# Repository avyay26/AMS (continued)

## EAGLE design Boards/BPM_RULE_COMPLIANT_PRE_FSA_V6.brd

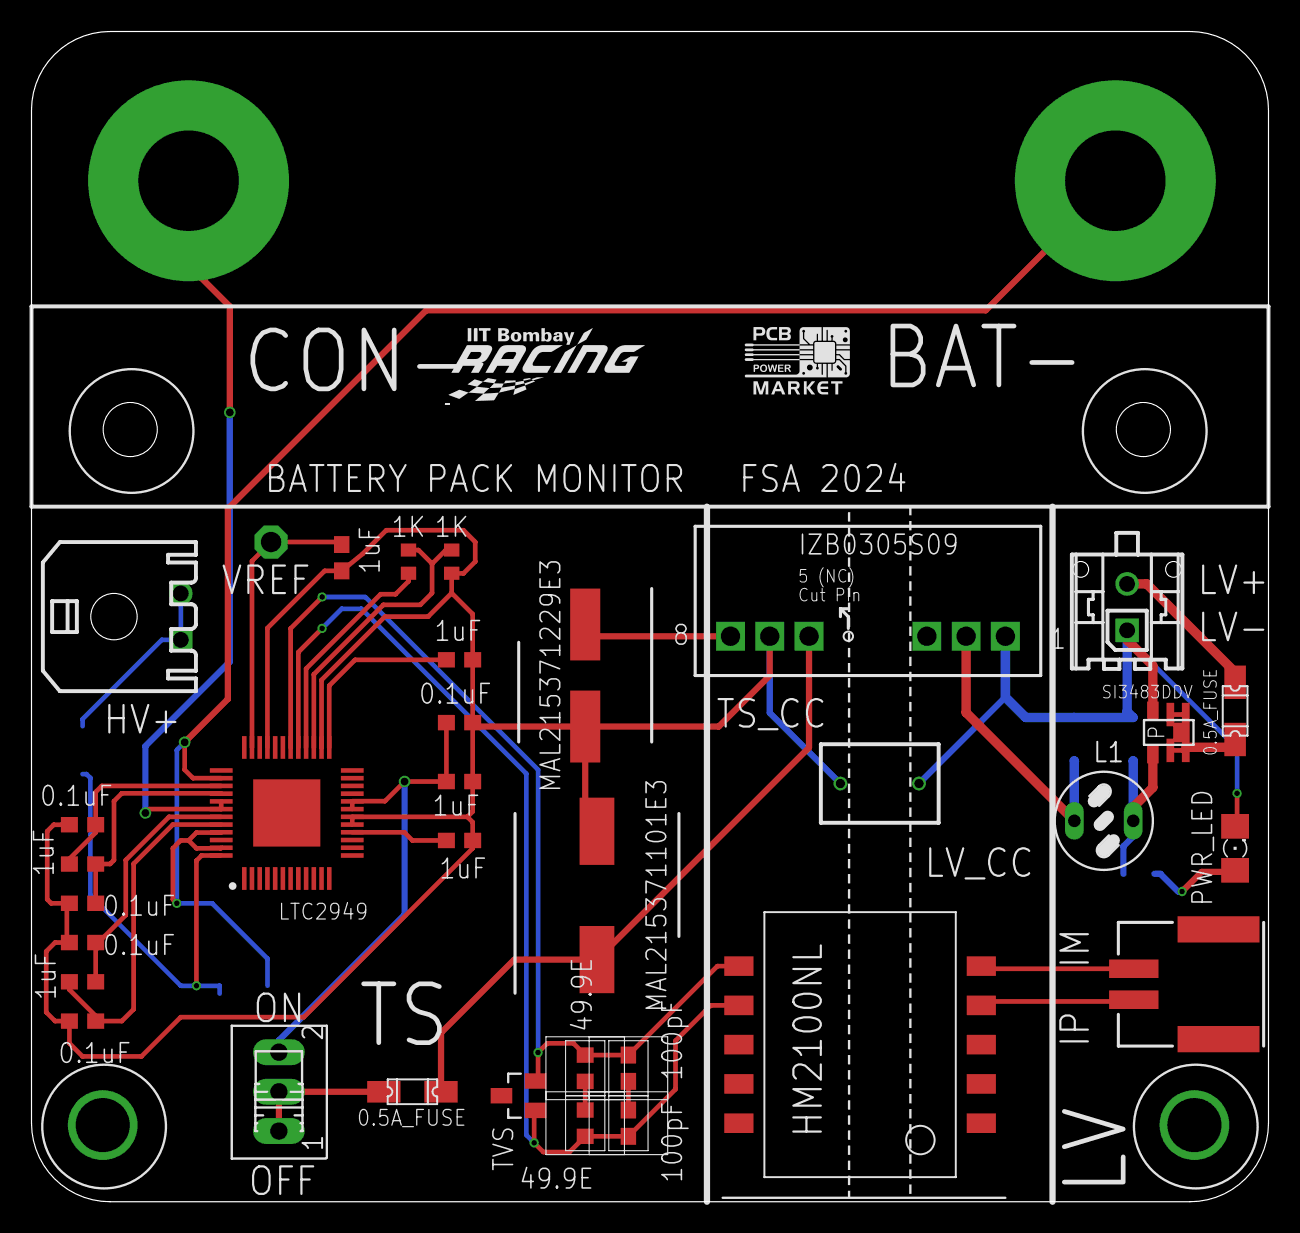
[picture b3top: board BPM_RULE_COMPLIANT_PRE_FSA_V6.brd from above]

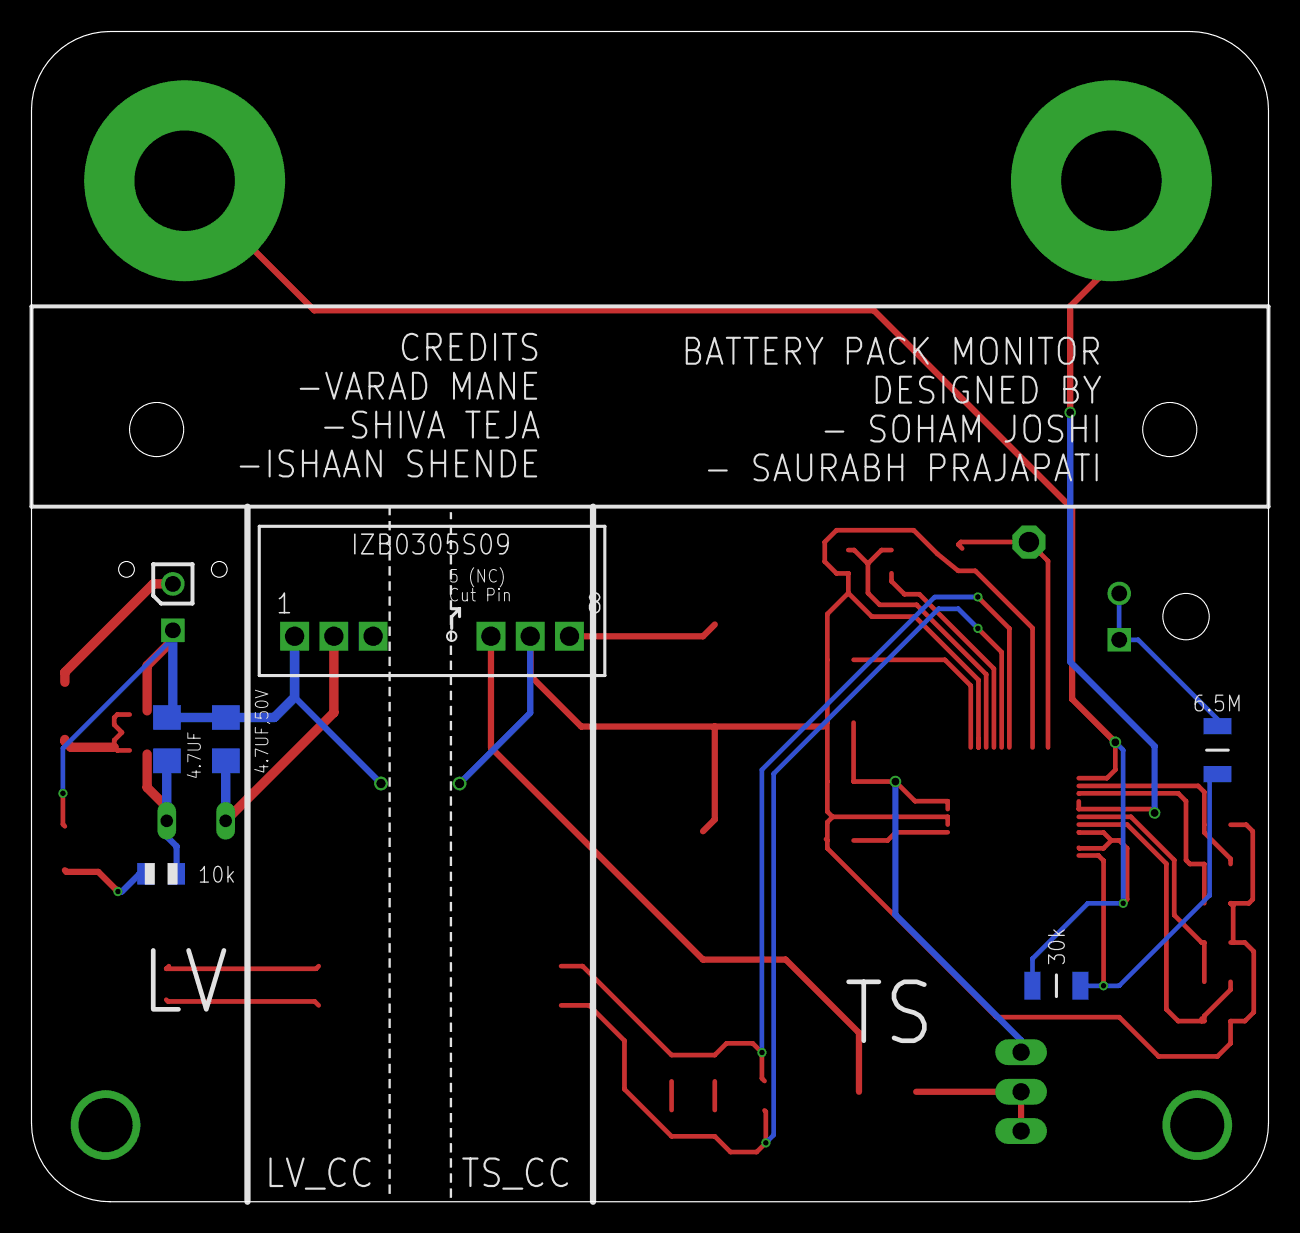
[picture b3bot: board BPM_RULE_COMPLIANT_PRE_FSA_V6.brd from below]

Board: 2 copper layers, 80.0 x 75.7 mm, 41 parts (5 on the bottom side), 30 nets.

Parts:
4.7UF, 4.7UF,50V: C1206
BYP1_FIL, BYP2_FIL: 1uF; C0603
C2: MAL215371101E3; CAPAE1060X1060N
C3: MAL215371229E3; CAPAE860X680N
C15: TPPAD1-13; P1-13
C16, C17: 100pF; C0603
DVCC_FIL: 1uF; C0603
F1, F2: 1206L
HM2100NL: HM2100NL
HV+: 43650-0200
I1G_FIL, I1_G_FIL, I2G_FIL1, I2_G_FIL1: 0.1uF; C0603
I1_FIL, I2_FIL1: 1uF; C0603
IC1: LTC2949HLXE#3ZZPBF; QFP50P900X900X160-49N
IM1: TVS; SOT23
J1: 502352-0200; 5023520200
L1: 82114R
POWER_SUPPLY: 43045-0212
PWR_LED: FKIT-LED-1206
R14: 30k; RESC3216X70N
R15, R16: 1K; RESC1608X50N
R17: 6.5M; RESC3216X70N
R20: 10k; R0805
RM1, RM2: 49.9E; R0603
S1: STS121PC04
S_G_BY: 0.1uF; C0603
U$1: BPM_CONV
U$2: 80-C330C102KGR5TATU
U$6: LOGO_PCBPOWER; 270X170
U$10: TSOP-6_PMOS
U$22: RACING_LOGO_190MIL
VREF_DECOUPLE1: 1uF; C0603

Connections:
12VIN: 4.7UF.1, L1.2, R20.1, U$10.S
12V_ACU_TO_BPM: F2.P$2, U$10.1, U$10.2, U$10.5, U$10.6, U$10.D
+12V: C2.1, F1.P$2, U$1.6
BATP: IC1.48, R14.2, R17.1
BYP1: BYP1_FIL.2, IC1.16
BYP2: BYP2_FIL.1, IC1.25
CF1M: I1G_FIL.1, I1_FIL.1, IC1.43
CF1P: I1_FIL.2, I1_G_FIL.2, IC1.44
CF2M: I2_FIL1.2, I2_G_FIL1.1, IC1.40
CF2P: I2G_FIL1.1, I2_FIL1.1, IC1.39
GND: BYP1_FIL.1, BYP2_FIL.2, C2.2, C3.2, DVCC_FIL.1, I1G_FIL.2, I1_G_FIL.1, I2G_FIL1.2, I2_G_FIL1.2, IC1.17, IC1.18, IC1.26, IC1.33, R16.2, S_G_BY.1, U$1.7, U$2.P$1, VREF_DECOUPLE1.1
GNDIN: 4.7UF.2, 4.7UF,50V.2, POWER_SUPPLY.P$1, PWR_LED.C, U$1.1, U$2.P$2, U$10.G
HV+: HV+.P$1, HV+.P$2, R17.2
HV-: IC1.38, IC1.45, IC1.47, R14.1
I1M: IC1.41, IC1.42
IBIAS: IC1.28, R15.1
ICMP: IC1.27, R15.2, R16.1
ISOA_M: C17.2, HM2100NL.6, IC1.30, IM1.2, RM2.1
ISOA_P: C16.1, HM2100NL.7, IC1.29, IM1.1, RM1.2
ISOB_M: HM2100NL.5, J1.2
ISOB_P: HM2100NL.4, J1.1
N$: RM1.1, RM2.2
unnamed: 4.7UF,50V.1, L1.1, U$1.2
unnamed: F2.P$1, POWER_SUPPLY.P$2
unnamed: PWR_LED.A, R20.2
unnamed: F1.P$1, S1.1, S1.2
unnamed: C16.2, C17.1
RIPPLE: C3.1, U$1.8
VCC: DVCC_FIL.2, IC1.19, IC1.20, S1.3, S_G_BY.2
VREF: C15.TP, IC1.35, VREF_DECOUPLE1.2

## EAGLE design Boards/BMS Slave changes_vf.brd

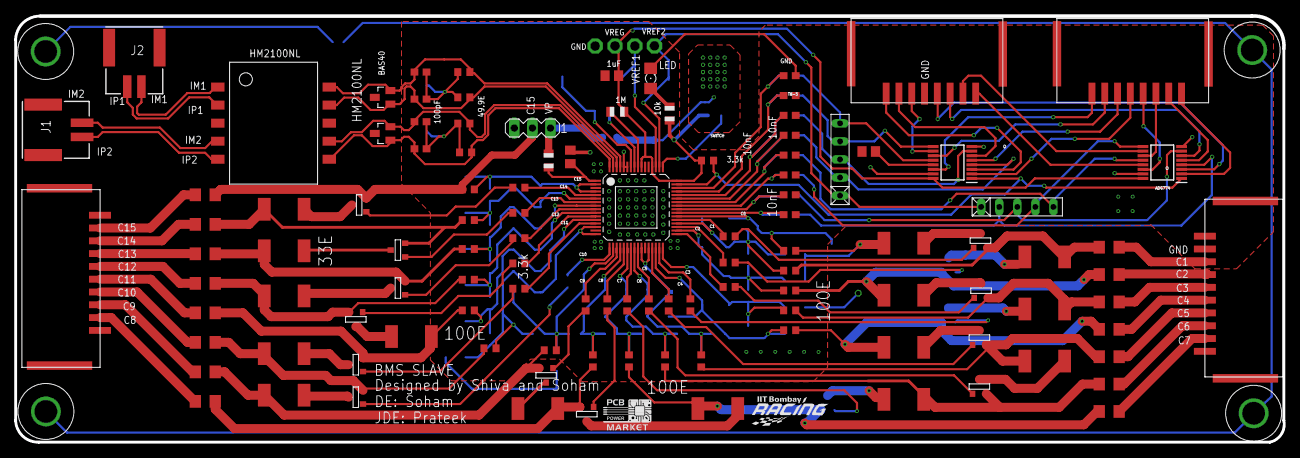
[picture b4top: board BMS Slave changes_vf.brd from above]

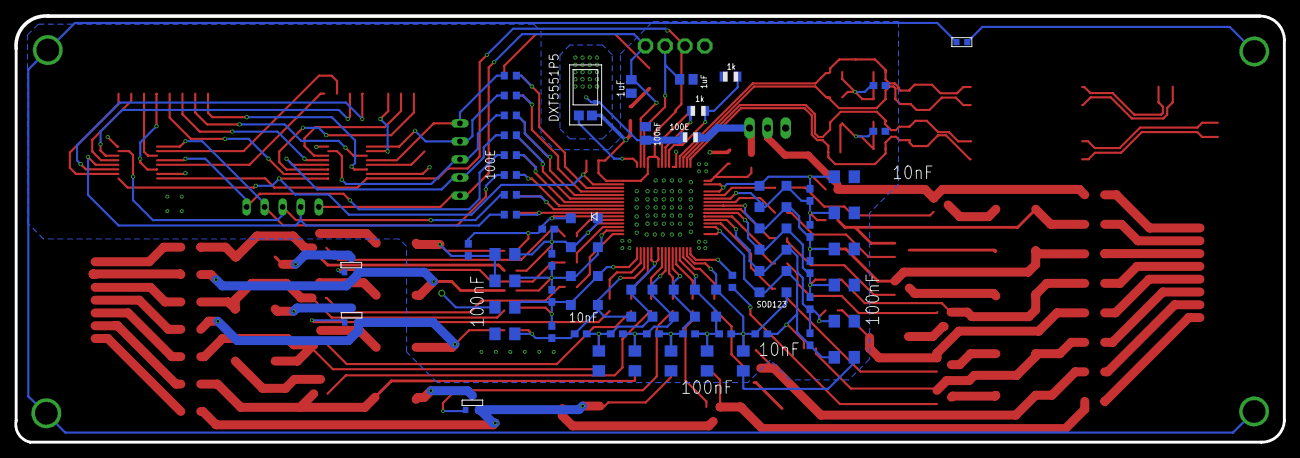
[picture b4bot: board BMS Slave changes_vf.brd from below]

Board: 2 copper layers, 178.5 x 60.0 mm, 185 parts (68 on the bottom side), 146 nets.

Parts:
C1, C175, C177: 1uF; C0805
C2, C3, C5, C6: 100pF; C0603
C4, C8: 10nF; C0603
C173, C176: 100nF; C0805
D1, D2, D3, D4, D5, D7, D8, D9, D10, D11, D12, D13, D14, D15, D16: SOD123
DEMUX1, DEMUX2: ADG774ABRQZ; SOP64P600X175-16N
E0, E1, E2, E3, E4, E5, E7, E8, E9, E10, E11, E12, E13, E14, E15, E16, E18, E19, E20, E21, E22, E23, E24, E25: 100E; R0603
F1, F2, F3, F4, F5, F7, F8, F9, F10, F11, F12, F13, F14, F15, F16: 100nF; C1206
IM1, IM2: BAS40-05; SOT23
J1, J2: 502352-0200; 5023520200
K1, K2, K3, K4, K5, K7, K8, K9, K10, K11, K12, K13, K14, K15, K16, K17: 3.3K; R0603
LED1: 1206
M1, M2, M3, M4, M5, M7, M8, M9, M10, M11, M12, M13, M14, M15, M16: SOT-23
P0, P1, P2, P3, P4, P6, P7, P8, P9, P10, P11, P12, P13, P14, P15: 33E; R2512
R1: 5k; R0805
R2: OE; R0603
R3: 100K; R0805
R157, R161: 100E; R0805
R159, R160: 1k; R0805
R162: 1M; R0805
RM1, RM2, RM3, RM4: 49.9E; R0603
RN2, RN3: 10k; RN-5
SV1: MA03-1
T0, T1, T2, T3, T4, T5, T7, T8, T9, T10, T11, T12, T13, T14, T15, T16, T18, T19, T20, T21, T22, T23, T24, T25: 10nF; C0603
TP1, TP6, TP7, TP8: TPPAD1-13; P1-13
U$1: HM2100NL
U$2: DXT5551P5
U$3: LTC6813
U$4: IITBR_LOGO
U$5, U$6: 1X10NANOMQS
U$7: LOGO_PCBPOWER; 270X170
U$8, U$10: NEWBMS
U$9, U$13, U$14, U$15, U$16, U$17, U$18, U$19, U$20, U$21, U$23, U$24, U$25, U$26, U$27: PTC-FUSE; 1206

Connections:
C: C173.1, R157.1, U$2.C
C01: E1.1, M1.2, P1.2, U$27.2
C02: E2.1, M2.2, P2.2, U$26.2
C03: E3.1, M3.2, P3.2, U$25.2
C04: E4.1, M4.2, P4.2, U$24.2
C05: E5.1, M5.2, P6.2, U$23.2
C06: E7.1, M7.2, P7.2, U$21.2
C07: E8.1, M8.2, P8.2, U$20.2
C08: E9.1, M9.2, P9.2, U$19.2
C09: E10.1, M10.2, P10.2, U$18.2
C10: E11.1, M11.2, P11.2, U$17.2
C11: E12.1, M12.2, P12.2, U$16.2
C12: E13.1, M13.2, P13.2, U$15.2
C13: E14.1, M14.2, P14.2, U$14.2
C14: E15.1, M15.2, P15.2, U$13.2
C15: E16.1, M16.2, SV1.2, U$9.2
C_01: U$6.P$3, U$27.1
C_02: U$6.P$4, U$26.1
C_03: U$6.P$5, U$25.1
C_04: U$6.P$6, U$24.1
C_05: U$6.P$7, U$23.1
C_06: U$6.P$8, U$21.1
C_07: U$6.P$9, U$20.1
C_08: U$5.P$2, U$19.1
C_09: U$5.P$3, U$18.1
C_10: U$5.P$4, U$17.1
C_11: U$5.P$5, U$16.1
C_12: U$5.P$6, U$15.1
C_13: U$5.P$7, U$14.1
C_14: U$5.P$8, U$13.1
C_15: U$5.P$9, U$9.1
C_17: D16.C, E16.2, F16.1, T16.1, U$3.C17, U$3.C18
C_18: D15.C, D16.A, E15.2, F15.1, T15.1, T16.2, U$3.C16
C_20: D14.C, D15.A, E14.2, F14.1, T14.1, T15.2, U$3.C15
C_21: K10.1, M10.3
C_22: D13.C, D14.A, E13.2, F13.1, T13.1, T14.2, U$3.C14
C_23: D9.C, D10.A, E9.2, F9.1, T9.1, T10.2, U$3.C9
C_24: D12.C, D13.A, E12.2, F12.1, T12.1, T13.2, U$3.C13
C_26: D8.C, D9.A, E8.2, F8.1, T8.1, T9.2, U$3.C8
C_27: D10.C, D11.A, E10.2, F10.1, T10.1, T11.2, U$3.C10
C_28: D11.C, D12.A, E11.2, F11.1, T11.1, T12.2, U$3.C11, U$3.C12
C_30: D7.C, D8.A, E7.2, F7.1, T7.1, T8.2, U$3.C7
C_33: D5.C, D7.A, E5.2, F5.2, T5.1, T7.2, U$3.C5, U$3.C6
C_35: D4.C, D5.A, E4.2, F4.2, T4.1, T5.2, U$3.C4
C_37: D3.C, D4.A, E3.2, F3.2, T3.1, T4.2, U$3.C3
C_38: D2.C, D3.A, E2.2, F2.2, T2.1, T3.2, U$3.C2
C_41: D1.A, E0.2, T0.1, T1.2, U$3.C0
C_42: D1.C, D2.A, E1.2, F1.2, T1.1, T2.2, U$3.C1
D13: K13.2, U$3.S14
GND: C1.2, C4.1, C8.1, C173.2, C175.2, C176.2, C177.2, DEMUX1.8, DEMUX1.15, DEMUX2.8, DEMUX2.15, E0.1, F1.1, F2.1, F3.1, F4.1, F5.1, F7.2, F8.2, F9.2, F10.2, F11.2, F12.2, F13.2, F14.2, F15.2, F16.2, LED1.C, P0.2, R3.2, R160.1, T0.2, T18.2, T19.2, T20.2, T21.2, T22.2, T23.2, T24.2, T25.2, TP8.TP, U$3.V-, U$3.V--, U$6.P$2, U$8.P$5
ISO_1_IN_N: C3.2, IM2.2, RM1.1, U$1.7, U$3.IMB
ISO_1_IN_P: C2.1, IM2.1, RM2.2, U$1.6, U$3.IPB
ISO_1_N: J1.1, U$1.4
ISO_1_P: J1.2, U$1.5
ISO_2_IN_N: C6.2, IM1.2, RM4.1, U$1.10, U$3.CSB(IMA)
ISO_2_IN_P: C5.1, IM1.1, RM3.2, U$1.9, U$3.SCK(IPA)
ISO_2_N: J2.1, U$1.1
ISO_2_P: J2.2, U$1.2
unnamed: DEMUX1.13, R3.1
unnamed: C2.2, C3.1, C4.2, RM1.2, RM2.1
unnamed: K15.2, U$3.S16
unnamed: C5.2, C6.1, C8.2, RM3.1, RM4.2
unnamed: R162.1, U$3.WDT
unnamed: E18.2, T18.1, U$3.GPIO4
unnamed: E19.2, T19.1, U$3.GPIO3
unnamed: E20.2, T20.1, U$3.GPIO2
unnamed: E21.2, T21.1, U$3.GPIO1
unnamed: K8.2, U$3.S8
unnamed: R159.1, R160.2, U$3.ICMP
unnamed: E23.2, T23.1, U$3.GPIO6
unnamed: E24.2, T24.1, U$3.GPIO7
unnamed: E25.2, T25.1, U$3.GPIO8
unnamed: E22.2, T22.1, U$3.GPIO5
unnamed: K16.2, M16.3
unnamed: M16.1, P15.1
unnamed: K15.1, M15.3
unnamed: M15.1, P14.1
unnamed: K14.1, M14.3
unnamed: M14.1, P13.1
unnamed: K13.1, M13.3
unnamed: M13.1, P12.1
unnamed: K12.1, M12.3
unnamed: M12.1, P11.1
unnamed: K11.1, M11.3
unnamed: M11.1, P10.1
unnamed: M10.1, P9.1
unnamed: K9.1, M9.3
unnamed: M9.1, P8.1
unnamed: M8.1, P7.1
unnamed: K7.2, U$3.S7
unnamed: M7.1, P6.1
unnamed: K16.1, U$3.S17
unnamed: K5.2, M5.3
unnamed: M5.1, P4.1
unnamed: K2.1, U$3.S2
unnamed: K4.2, M4.3
unnamed: M4.1, P3.1
unnamed: K3.2, M3.3
unnamed: M3.1, P2.1
unnamed: K2.2, M2.3
unnamed: M2.1, P1.1
unnamed: K1.2, M1.3
unnamed: M1.1, P0.1
unnamed: K14.2, U$3.S15
unnamed: K12.2, U$3.S13
unnamed: K11.2, U$3.S11
unnamed: K10.2, U$3.S10
unnamed: K9.2, U$3.S9
unnamed: K8.1, M8.3
unnamed: K7.1, M7.3
unnamed: K5.1, U$3.S5
unnamed: K4.1, U$3.S4
unnamed: K3.1, U$3.S3
unnamed: K1.1, U$3.S1
unnamed: U$2.B, U$3.DRIVE
unnamed: R159.2, U$3.IBIAS
unnamed: C176.1, R161.1, U$3.V+
P_TEMP1: DEMUX2.2, U$10.P$1
P_TEMP2: DEMUX2.5, U$10.P$2
P_TEMP3: DEMUX2.11, U$10.P$3
P_TEMP4: DEMUX2.14, U$10.P$4
P_TEMP5: DEMUX1.2, U$10.P$5
P_TEMP6: DEMUX1.5, U$10.P$6
P_TEMP7: DEMUX1.11, U$10.P$7
P_TEMP8: DEMUX1.14, U$10.P$8
P_TEMP9: DEMUX2.3, U$8.P$4
P_TEMP10: DEMUX2.6, U$8.P$3
P_TEMP11: DEMUX2.10, U$8.P$2
P_TEMP12: DEMUX2.13, U$8.P$1
P_TEMP13: DEMUX1.3, U$8.P$8
P_TEMP14: DEMUX1.6, U$8.P$7
P_TEMP15: DEMUX1.10, U$8.P$6
R: LED1.A, R1.1
SWITCH_TEMP: DEMUX1.1, DEMUX2.1, K17.1, U$3.GPIO9
TEMP1: DEMUX2.4, E21.1, RN2.2
TEMP2: DEMUX2.7, E20.1, RN2.3
TEMP3: DEMUX2.9, E19.1, RN2.4
TEMP4: DEMUX2.12, E18.1, RN2.5
TEMP5: DEMUX1.4, E22.1, RN3.2
TEMP6: DEMUX1.7, E23.1, RN3.3
TEMP7: DEMUX1.9, E24.1, RN3.4
TEMP8: DEMUX1.12, E25.1, RN3.5
VP: R157.2, R161.2, SV1.1
VREF1: C175.1, TP7.TP, U$3.VREF1
VREF2: C177.1, RN2.1, RN3.1, TP1.TP, U$3.VREF2
VREG: C1.1, DEMUX1.16, DEMUX2.16, K17.2, R1.2, R162.2, TP6.TP, U$2.E, U$3.DTEN, U$3.ISOMB, U$3.VREG

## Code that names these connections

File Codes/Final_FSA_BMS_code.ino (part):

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

// defined by me 
#define BMS_FLT_3V3 18              // PIN 18 ( A4 ) selected as BMS ERROR pin on teensy can check on master
#define FAN_MBED 19                 // FAN mbed signal to ACU
#define CH_EN_MBED 22               // charger enable signal to ACU
#define PEC_ERR_PIN 9               // to switch error state led on master
#define VOLT_ERR_PIN 7              // to switch error state led on master
#define TEMP_ERR_PIN 8              // to switch error state led on master

#define voltTimer 400               // Time for voltage loop to go on in its error checking mode
#define tempTimer 900                // Time for temperature loop to go on in its error checking mode
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
#define UI_BUFFER_SIZE 64

#define RES 30000                   // Resistor divider for BATP and BATM
#define RES_SUM 6520000
#define POT_DIV_BPM 76.5   // Voltage Multiplier for BPM

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	digitalWrite(LTCDEF_GPO, HIGH);
	pinMode(LTCDEF_GPO, OUTPUT);

  pinMode( PEC_ERR_PIN , OUTPUT );
  pinMode( VOLT_ERR_PIN , OUTPUT );
  pinMode( TEMP_ERR_PIN , OUTPUT );
  pinMode( BMS_FLT_3V3 , OUTPUT );     // Bpin defined for sending signal to ACU for BMS error
  pinMode( FAN_MBED , OUTPUT );
  pinMode( CH_EN_MBED , OUTPUT );

  
  initialiseSDcard();
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      case 1:
        if ( tempFlag )
        {
          digitalWriteFast(TEMP_ERR_PIN,HIGH);
        }
        else
        {
          digitalWriteFast(TEMP_ERR_PIN,LOW);
        }
        break;
      case 2:
        if ( voltFlag && tempFlag )
        {
          digitalWriteFast(VOLT_ERR_PIN,HIGH);
          digitalWriteFast(TEMP_ERR_PIN,HIGH);
        }
        break;
    }
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
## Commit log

2024-08-10 Create Slave board
2024-08-10 Create Guidelines
2024-08-10 Create All AMS Codes And libraries
